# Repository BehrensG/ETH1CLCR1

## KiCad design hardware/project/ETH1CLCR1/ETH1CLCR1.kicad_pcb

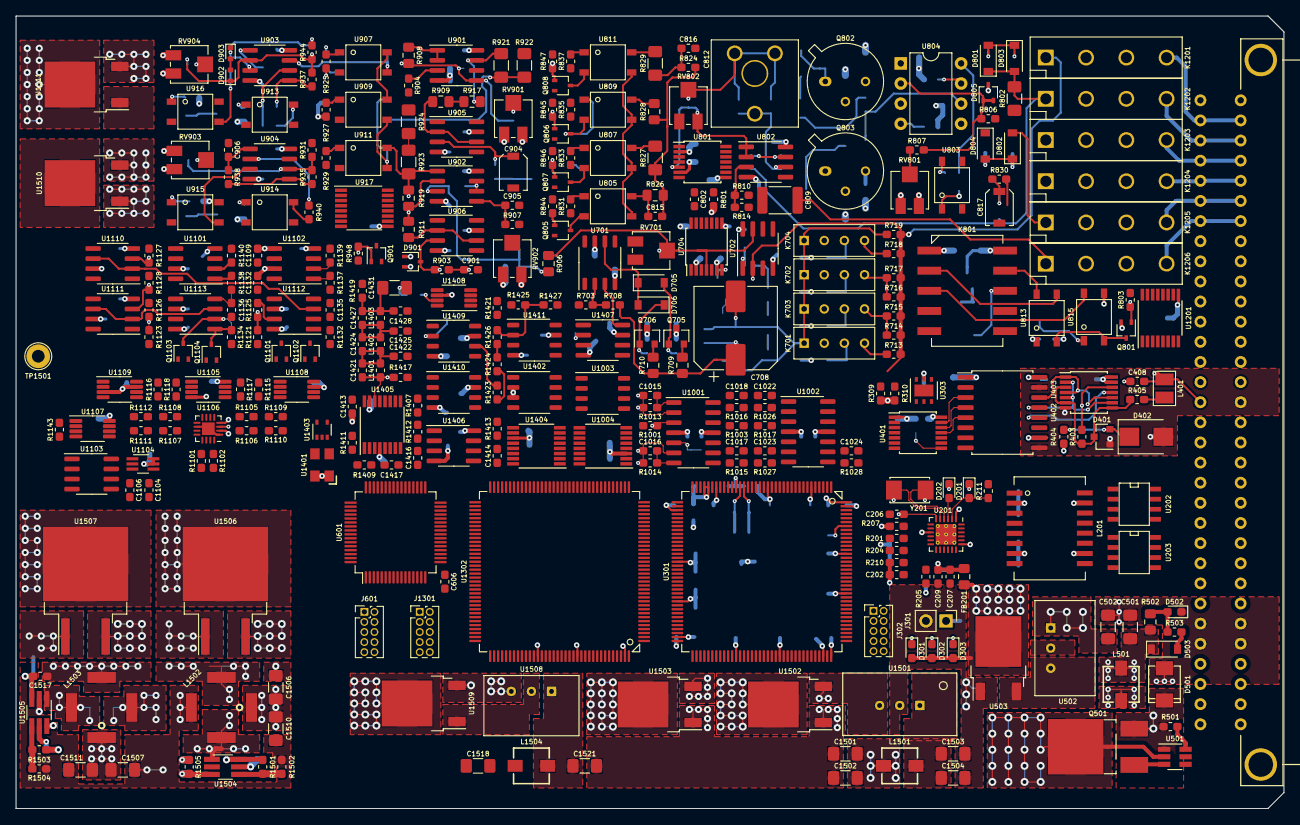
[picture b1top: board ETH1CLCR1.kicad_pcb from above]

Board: 8 copper layers, 160.0 x 100.0 mm, 744 parts (0 on the bottom side), 493 nets.

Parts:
C201, C204, C303, C305, C612, C613, C1302, C1304: 8p; C_0603_1608Metric_Pad1.05x0.95mm_HandSolder
C202, C205, C208, C209, C210, C211, C212, C301, C302, C304, C306, C308, C310, C312, C313, C314, C315, C316, C317, C318, C319, C321, C322, C401, C402, C403, C405, C407, C601, C602, C603, C604, C605, C606, C608, C611, C705, C706, C707, C709, C710, C711, C712, C803, C804, C805, C806, C807, C808, C810, C901, C902, C911, C912, C913, C914, C915, C916, C917, C918, C919, C920, C921, C922, C923, C1001, C1003, C1005, C1006, C1007, C1009, C1010, C1101, C1105, C1106, C1108, C1109, C1110, C1113, C1114, C1115, C1116, C1117, C1118, C1119, C1120, C1123, C1124, C1125, C1126, C1127, C1128, C1129, C1130, C1131, C1132, C1139, C1140, C1201, C1301, C1303, C1305, C1308, C1309, C1311, C1312, C1313, C1314, C1315, C1316, C1317, C1319, C1401, C1402, C1404, C1405, C1407, C1408, C1409, C1410, C1411, C1412, C1415, C1416, C1418, C1423, C1426, C1429, C1430, C1432, C1433, C1437, C1438: 100n; C_0603_1608Metric_Pad1.05x0.95mm_HandSolder
C203: 470p; C_0603_1608Metric_Pad1.05x0.95mm_HandSolder
C206, C207, C311, C320, C404, C406, C607, C609, C714, C802, C1004, C1008, C1103, C1104, C1107, C1310, C1318, C1406, C1512, C1513: 1u; C_0603_1608Metric_Pad1.05x0.95mm_HandSolder
C213, C214: 1n/1kV; C_1206_3216Metric_Pad1.42x1.75mm_HandSolder
C307, C309, C610, C1306, C1307: 2u2; C_0805_2012Metric_Pad1.15x1.40mm_HandSolder
C408, C813: 47p; C_0603_1608Metric_Pad1.05x0.95mm_HandSolder
C501, C502, C1501, C1502, C1503, C1504, C1506, C1507, C1518, C1521: 10u/50V; C_1206_3216Metric_Pad1.42x1.75mm_HandSolder
C503, C504, C1505, C1508, C1509, C1526, C1529: 10u/16V; C_1206_3216Metric_Pad1.42x1.75mm_HandSolder
C701, C702, C703, C704, C801, C818, C819, C820, C821, C822, C908, C909, C910, C1133, C1134, C1137, C1138: 10p; C_0603_1608Metric_Pad1.05x0.95mm_HandSolder
C708: 220u; CP_Elec_10x10
C713: 43p/200V; C_0603_1608Metric_Pad1.05x0.95mm_HandSolder
C715, C716, C823, C824: 10u/35V; C_1206_3216Metric_Pad1.42x1.75mm_HandSolder
C809: 1u/100V; C_1812_4532Metric_Pad1.30x3.40mm_HandSolder
C811: C; C_0603_1608Metric_Pad1.05x0.95mm_HandSolder
C812: BFC280908002; BFC2
C814: 33p/200V; C_0603_1608Metric_Pad1.05x0.95mm_HandSolder
C815: 6800p/200V; C_0603_1608Metric_Pad1.05x0.95mm_HandSolder
C816: 39p; C_0603_1608Metric_Pad1.05x0.95mm_HandSolder
C817, C904: JZ100; JZ
C903: 7p5; C_0603_1608Metric_Pad1.05x0.95mm_HandSolder
C905: 15p; C_0603_1608Metric_Pad1.05x0.95mm_HandSolder
C906: 390p; C_0603_1608Metric_Pad1.05x0.95mm_HandSolder
C907: 220p; C_0603_1608Metric_Pad1.05x0.95mm_HandSolder
C1002, C1102, C1403, C1435: 10u; C_0805_2012Metric_Pad1.15x1.40mm_HandSolder
C1011, C1012, C1013, C1014, C1019, C1020, C1021, C1414: 220n; C_0603_1608Metric_Pad1.05x0.95mm_HandSolder
C1015, C1016, C1017, C1018, C1022, C1023, C1024, C1121, C1122, C1135, C1136, C1419: 1n; C_0603_1608Metric_Pad1.05x0.95mm_HandSolder
C1111, C1112: 3300p; C_0603_1608Metric_Pad1.05x0.95mm_HandSolder
C1413, C1417: 10n; C_0603_1608Metric_Pad1.05x0.95mm_HandSolder
C1420, C1428: 22p; C_0603_1608Metric_Pad1.05x0.95mm_HandSolder
C1421, C1516, C1517: 4p7; C_0603_1608Metric_Pad1.05x0.95mm_HandSolder
C1422, C1425: 56p; C_0603_1608Metric_Pad1.05x0.95mm_HandSolder
C1424: 18p; C_0603_1608Metric_Pad1.05x0.95mm_HandSolder
C1427: 12p; C_0603_1608Metric_Pad1.05x0.95mm_HandSolder
C1431: 10u; C_1206_3216Metric_Pad1.42x1.75mm_HandSolder
C1434, C1436: 1p5; C_0603_1608Metric_Pad1.05x0.95mm_HandSolder
C1510, C1511, C1519, C1520, C1522, C1523, C1524, C1525, C1527, C1528: 4u7/50V; C_1206_3216Metric_Pad1.42x1.75mm_HandSolder
C1514, C1515: 1u/HC; C_1206_3216Metric_Pad1.42x1.75mm_HandSolder
D201: YELLOW; LED_0603_1608Metric_Pad1.05x0.95mm_HandSolder
D202, D302: GREEN; LED_0603_1608Metric_Pad1.05x0.95mm_HandSolder
D301, D502: RED; LED_0603_1608Metric_Pad1.05x0.95mm_HandSolder
D303: BLUE; LED_0603_1608Metric_Pad1.05x0.95mm_HandSolder
D401: BAV99; SOT-23
D402: SMBJ5.0A; D_SMB
D403: SD36C-01FTG; D_SOD-323_HandSoldering
D501: SM6T30AY; DO_214AA_REV
D503: MMSZ5249B; D_SOD-123
D701, D702, D703, D704, D705, D706, D801, D802, D803, D804, D806, D807, D808, D809, D810, D811, D812: 1N4148; D_SOD-123
D707, D708: CMDZ5256B TR; D_SOD-323_HandSoldering
D805, D901: BAT54SW; SOT-323_SC-70
D902, D903: MM5Z5V1T5G; D_SOD-523
D1401: SD103ATW; SOT-363_SC-70-6
D1501, D1502: PMEG6010EP,115; D_SOD-128
F501: MF-LSMF185/33X; Fuse_SMD2920
FB201, FB301, FB601, FB1301: 742792031; L_0805_2012Metric_Pad1.15x1.40mm_HandSolder
J301: Conn_02x01; PinHeader_1x02_P2.54mm_Vertical
J302, J601, J1301: 20021111-00010T4LF; PinHeader_2x05_P1.27mm_Vertical
J1201: C64AC; Socket_DIN41612-CaseC1-AC-Male-64Pin-2rows
K701, K702, K703, K704: 9012
K801: TQ2SA-5V; SA
K1201, K1202, K1203, K1204, K1205, K1206: HE3621A0510; HE360_x-5050462-8
L201: 749010012A
L401: CW252016-R33G; CW252016
L501, L1501, L1504: TCK-141
L1401, L1402, L1403: 4u7; L_0603_1608Metric_Pad1.05x0.95mm_HandSolder
L1502, L1503: 74489440068
Q501: IRFR5410; TO-252-2_Rectifier
Q701, Q702, Q703, Q704, Q801, Q804, Q805, Q806, Q807, Q808, Q901, Q902, Q903, Q1101, Q1102, Q1103, Q1104: BC847W; SOT-323_SC-70
Q705: MMBT4401L; SOT-23
Q706: MMBT4403L; SOT-23
Q802: 2N2218A; TO-39-3
Q803: 2N2904A; TO-39-3
R201, R202, R204, R205: 33; R_0603_1608Metric_Pad1.05x0.95mm_HandSolder
R203, R206, R207, R208, R209, R211, R304, R307, R308, R401, R603, R604, R701, R702, R704, R705, R718, R803, R810, R813, R815, R818, R824, R830, R841, R844, R845, R846, R847, R903, R904, R905, R907, R935, R938, R944, R948, R949, R950, R1122, R1124, R1135, R1136, R1139, R1141, R1142, R1303, R1304, R1401, R1405, R1407, R1424, R1428: 10k; R_0603_1608Metric_Pad1.05x0.95mm_HandSolder
R210: 1k5; R_0603_1608Metric_Pad1.05x0.95mm_HandSolder
R212: 12k1; R_0603_1608Metric_Pad1.05x0.95mm_HandSolder
R213, R214: 270; R_0603_1608Metric_Pad1.05x0.95mm_HandSolder
R215, R216, R217, R218: 49R9; R_0603_1608Metric_Pad1.05x0.95mm_HandSolder
R219: 1M/1kV; R_1206_3216Metric_Pad1.42x1.75mm_HandSolder
R220, R221: 75/1%; R_0603_1608Metric_Pad1.05x0.95mm_HandSolder
R301, R303, R831, R832, R833, R834, R835, R836, R837, R838, R925, R926, R927, R928, R929, R930, R936, R943, R945, R947: 680; R_0603_1608Metric_Pad1.05x0.95mm_HandSolder
R302: 560; R_0603_1608Metric_Pad1.05x0.95mm_HandSolder
R305, R306, R309, R310, R601, R602, R1301, R1302: 4k7; R_0603_1608Metric_Pad1.05x0.95mm_HandSolder
R402: 14k7; R_0603_1608Metric_Pad1.05x0.95mm_HandSolder
R403, R806, R1101, R1102, R1105, R1106, R1107, R1108, R1115, R1116, R1137, R1138: 100; R_0603_1608Metric_Pad1.05x0.95mm_HandSolder
R404, R931, R932, R937, R940, R942, R946, R1001, R1002, R1003, R1004, R1017, R1018, R1019, R1413, R1423, R1425, R1426, R1427: 1k; R_0603_1608Metric_Pad1.05x0.95mm_HandSolder
R405, R811, R812: 47; R_0603_1608Metric_Pad1.05x0.95mm_HandSolder
R406, R816, R817: 51R1; R_0603_1608Metric_Pad1.05x0.95mm_HandSolder
R501, R719, R939, R1013, R1014, R1015, R1016, R1026, R1027, R1028, R1127, R1128, R1131, R1132, R1133, R1134, R1416: 100k; R_0603_1608Metric_Pad1.05x0.95mm_HandSolder
R502: 6k8/0.5W; R_0805_2012Metric_Pad1.15x1.40mm_HandSolder
R503: 370; R_0603_1608Metric_Pad1.05x0.95mm_HandSolder
R703, R708, R716, R717: 2k; R_0603_1608Metric_Pad1.05x0.95mm_HandSolder
R706, R707: 15k; R_0603_1608Metric_Pad1.05x0.95mm_HandSolder
R709, R710: 27/.25W; R_0805_2012Metric_Pad1.15x1.40mm_HandSolder
R711: OPT; R_0603_1608Metric_Pad1.05x0.95mm_HandSolder
R712, R809, R840, R842, R843: 330; R_0603_1608Metric_Pad1.05x0.95mm_HandSolder
R713: 10; R_0603_1608Metric_Pad1.05x0.95mm_HandSolder
R714, R715: 200; R_0603_1608Metric_Pad1.05x0.95mm_HandSolder
R720: 56; R_0603_1608Metric_Pad1.05x0.95mm_HandSolder
R721: 205; R_0603_1608Metric_Pad1.05x0.95mm_HandSolder
R722, R801: 2k2; R_0603_1608Metric_Pad1.05x0.95mm_HandSolder
R723, R808: 550; R_0603_1608Metric_Pad1.05x0.95mm_HandSolder
R802: 1k/.25W; R_1206_3216Metric_Pad1.42x1.75mm_HandSolder
R804, R805: 21R5/.5W; R_0805_2012Metric_Pad1.15x1.40mm_HandSolder
R807: 10M; R_0603_1608Metric_Pad1.05x0.95mm_HandSolder
R814: 5M6; R_0603_1608Metric_Pad1.05x0.95mm_HandSolder
R819: 3k3; R_0603_1608Metric_Pad1.05x0.95mm_HandSolder
R820, R823: 261/.5W; R_0805_2012Metric_Pad1.15x1.40mm_HandSolder
R821, R822: 2R7/.5W; R_0805_2012Metric_Pad1.15x1.40mm_HandSolder
R825: 90k; R_1206_3216Metric_Pad1.42x1.75mm_HandSolder
R826: 10; R_0805_2012Metric_Pad1.15x1.40mm_HandSolder
R827, R922, R924: 100; R_1206_3216Metric_Pad1.42x1.75mm_HandSolder
R828: 1k01; R_0805_2012Metric_Pad1.15x1.40mm_HandSolder
R829: 1k; R_1206_3216Metric_Pad1.42x1.75mm_HandSolder
R839: 13R3; R_0603_1608Metric_Pad1.05x0.95mm_HandSolder
R901, R902, R914, R920, R933, R1143, R1501, R1503, R1505, R1507: 1M; R_0603_1608Metric_Pad1.05x0.95mm_HandSolder
R906, R908, R909, R910, R911, R913, R917, R919: 3k01; R_0805_2012Metric_Pad1.15x1.40mm_HandSolder
R912, R915, R918, R1403, R1404, R1422: DNP; R_0603_1608Metric_Pad1.05x0.95mm_HandSolder
R916: NC; R_0603_1608Metric_Pad1.05x0.95mm_HandSolder
R921, R923: 900; R_1206_3216Metric_Pad1.42x1.75mm_HandSolder
R934, R941: 22k; R_0603_1608Metric_Pad1.05x0.95mm_HandSolder
R1005, R1007, R1009, R1011, R1020, R1022, R1024, R1414: 24k9; R_0603_1608Metric_Pad1.05x0.95mm_HandSolder
R1006, R1008, R1010, R1012, R1021, R1023, R1025, R1415: 33k2; R_0603_1608Metric_Pad1.05x0.95mm_HandSolder
R1103, R1104: 590; R_0603_1608Metric_Pad1.05x0.95mm_HandSolder
R1109, R1110, R1111, R1112, R1129, R1130: 50; R_0603_1608Metric_Pad1.05x0.95mm_HandSolder
R1113, R1114: 499; R_0603_1608Metric_Pad1.05x0.95mm_HandSolder
R1117, R1118, R1121, R1123: 12k; R_0603_1608Metric_Pad1.05x0.95mm_HandSolder
R1119, R1120, R1125, R1126: 52k3; R_0603_1608Metric_Pad1.05x0.95mm_HandSolder
R1140: 10K; R_0603_1608Metric_Pad1.05x0.95mm_HandSolder
R1402, R1406, R1418, R1420, R1421: 0; R_0603_1608Metric_Pad1.05x0.95mm_HandSolder
R1408: 4k22; R_0603_1608Metric_Pad1.05x0.95mm_HandSolder
R1409, R1411: 3k9; R_0603_1608Metric_Pad1.05x0.95mm_HandSolder
R1410, R1412: 1k96; R_0603_1608Metric_Pad1.05x0.95mm_HandSolder
R1417, R1419: 300; R_0603_1608Metric_Pad1.05x0.95mm_HandSolder
R1502, R1504: 287k; R_0603_1608Metric_Pad1.05x0.95mm_HandSolder
R1506: 97k6; R_0603_1608Metric_Pad1.05x0.95mm_HandSolder
R1508: 46k4; R_0603_1608Metric_Pad1.05x0.95mm_HandSolder
RV701, RV802: 3314J-1-501E; Potentiometer_Bourns_3314J_Vertical
RV801: 3314J-1-203E; Potentiometer_Bourns_3314J_Vertical
RV901, RV902: 3314J-1-103E; Potentiometer_Bourns_3314J_Vertical
RV903, RV904: 3314J-2-104E; Potentiometer_Bourns_3314J_Vertical
TP1501: 5006; TestPoint_Loop_D2.60mm_Drill1.6mm_Beaded
U201: LAN8742A; QFN-24-1EP_4x4mm_P0.5mm_EP2.6x2.6mm_ThermalVias
U202, U203: LC03-3.3; SO8E
U301: STM32F765ZGT6; TQFP-144_20x20mm_P0.5mm
U302, U602, U1301: 24LC08B-E/MS; MSOP-8_3x3mm_P0.65mm
U303: HDC1080; Texas_PWSON-N6
U401: TXB0104PW; TSSOP-14_4.4x5mm_P0.65mm
U402: ADuM5402; SOIC-16W_7.5x10.3mm_P1.27mm
U403: 74AC125; TSSOP-14_4.4x5mm_P0.65mm
U501: MAX5902; SOT-23-6_Handsoldering
U502: TSR1-2450; TSR1
U503, U1502, U1503: LM1117DTX-3.3/NOPB; TO-252-2
U601: STM32F413RGT6Tx; LQFP-64_10x10mm_P0.5mm
U701, U1409, U1410, U1411: LT1468; SSOP-8_3.9x5.05mm_P1.27mm
U702, U802, U901, U902, U903, U904, U1406: TL072; SOIC-8_3.9x4.9mm_P1.27mm
U703, U803, U805, U806, U807, U808, U809, U810, U811, U812, U813, U814, U815, U907, U908, U909, U910, U911, U912, U913, U914, U915, U916: AQY212GS
U704, U801: AD5293BRUZ-20; TSSOP-14_4.4x5mm_P0.65mm
U804: HA3-2525-5Z; DIP-8_W7.62mm
U905, U906: TL071; SOIC-8_3.9x4.9mm_P1.27mm
U917, U1201: ULN2003A; TSSOP-16_4.4x5mm_P0.65mm
U1001, U1002: TL074; SOIC-14_3.9x8.7mm_P1.27mm
U1003, U1402: REF192; SSOP-8_3.9x5.05mm_P1.27mm
U1004: DAC8568IBPWR; TSSOP-16_4.4x5mm_P0.65mm
U1101, U1102: ADG419BR; SOIC-8_3.9x4.9mm_P1.27mm
U1103: ADR4525BRZ; SOIC-8_3.9x4.9mm_P1.27mm
U1104: ADA4807-1AKSZ-R2; SOT-363_SC-70-6_Handsoldering
U1105, U1107: ADA4807-2ARM; MSOP-8_3x3mm_P0.65mm
U1106: AD7380; LFCSP-16-1EP_3x3mm_P0.5mm_EP1.6x1.6mm
U1108, U1109: LT6350; MSOP-8_3x3mm_P0.65mm
U1110, U1111: OPA602; SOIC-8_3.9x4.9mm_P1.27mm
U1112, U1113: PGA103; SOIC-8_3.9x4.9mm_P1.27mm
U1302: STM32H743ZI; TQFP-144_20x20mm_P0.5mm
U1401: ECS-3225SMV-500-GP-TR; ECS
U1403: 74AHCT1G08; SOT-353_SC-70-5
U1404: AD5689BRUZ; TSSOP-16_4.4x5mm_P0.65mm
U1405: AD9835; TSSOP-16_4.4x5mm_P0.65mm
U1407: DG419LDY; SOIC-8_3.9x4.9mm_P1.27mm
U1408: AD5453YRMZ; MSOP-8_3x3mm_P0.65mm
U1501: TSR2-2450; TSR2
U1504, U1505: LT8330_S6; TSOT-23-6_HandSoldering
U1506: MC7815BD2TG; TO-263-2
U1507: MC7915BD2TG; TO-263-2
U1508: TSR1-2490; TSR1
U1509: LM1117DTX-5.0/NOPB; TO-252-2
U1510: MC78M12ABDTRKG; TO-252-2
U1511: MC79M12CDTG; TO-252-2
Y201: NX5032GA-25.000M-LN-CD-1; NX5032GA
Y301, Y601, Y1301: NX3225GD-8MHZ-STD-CRA-3; NX3225GD

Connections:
+3.3VF: C601.1, C602.1, C603.1, C604.1, C605.1, C606.1, C607.1, C608.1, C707.1, C810.1, C1007.1, C1008.1, C1108.1, C1109.1, C1110.1, C1113.1, C1401.1, C1402.1, C1404.1, C1435.1, C1437.1, C1509.1, FB601.2, J601.1, R601.1, R602.1, R604.2, R722.1, R801.1, R840.1, R842.1, R843.1, R1401.1, R1403.1, R1405.1, R1407.1, U601.1, U601.19, U601.32, U601.48, U601.64, U602.8, U704.8, U801.8, U1004.3, U1101.5, U1102.5, U1106.2, U1106.4, U1401.1, U1401.4, U1403.5, U1404.11, U1405.4, U1407.5, U1408.6, U1503.2
+3.3VP: C1301.1, C1303.1, C1305.1, C1308.1, C1309.1, C1310.1, C1311.1, C1312.1, C1313.1, C1314.1, C1315.1, C1316.1, C1317.1, C1508.1, FB1301.2, J1301.1, R1301.1, R1302.1, R1304.1, U1301.8, U1302.6, U1302.17, U1302.30, U1302.39, U1302.52, U1302.62, U1302.72, U1302.84, U1302.95, U1302.108, U1302.121, U1302.131, U1302.143, U1302.144, U1502.2
+3V3: C202.1, C205.1, C301.1, C302.1, C304.1, C306.1, C308.1, C310.1, C311.1, C312.1, C313.1, C314.1, C315.1, C316.1, C317.1, C318.1, C319.1, C322.1, C402.1, C504.1, D301.2, D302.2, D303.2, FB201.2, FB301.2, J302.1, R206.1, R207.1, R208.1, R209.1, R210.1, R304.2, R305.1, R306.1, R308.1, R309.1, R310.1, R401.1, U201.9, U301.6, U301.17, U301.30, U301.39, U301.52, U301.62, U301.72, U301.84, U301.95, U301.108, U301.121, U301.131, U301.143, U301.144, U302.8, U303.5, U401.1, U503.2
+5V: C401.1, C403.1, C404.1, C503.1, U401.14, U402.1, U502.3, U503.3
+5VF: C923.1, C1001.1, C1002.1, C1101.1, C1102.1, C1114.1, C1116.1, C1118.1, C1120.1, C1124.1, C1201.1, C1403.1, C1405.1, C1407.1, C1413.1, C1529.1, D701.1, D702.1, D703.1, D704.1, D812.1, K701.2, K702.2, K703.2, K704.2, K801.1, K1201.2, K1202.2, K1203.2, K1204.2, K1205.2, K1206.2, R831.2, R832.2, R833.2, R834.2, R835.2, R836.2, R837.2, R838.2, R925.2, R926.2, R927.2, R928.2, R929.2, R930.2, R936.1, R943.1, R945.1, R947.1, U917.9, U1003.2, U1003.3, U1103.2, U1104.5, U1104.6, U1105.8, U1107.8, U1108.3, U1108.7, U1109.3, U1109.7, U1201.9, U1402.2, U1402.3, U1404.5, U1405.15, U1509.2
+5V_TRIG: C405.1, C406.1, C407.1, R404.1, U402.10, U402.16, U403.13, U403.14
+12VF: C805.1, C823.1, C911.1, C912.1, C913.1, C914.1, C915.1, C916.1, C1527.1, D901.2, R811.2, R815.1, R820.1, RV801.1, RV901.3, RV902.3, RV903.1, RV904.1, U802.8, U901.8, U902.8, U903.8, U904.8, U905.7, U906.7, U1510.3
+15VF: C705.1, C709.1, C710.1, C715.1, C807.1, C1003.1, C1009.1, C1115.1, C1119.1, C1125.1, C1126.1, C1129.1, C1130.1, C1408.1, C1409.1, C1423.1, C1429.1, C1433.1, C1524.1, Q705.3, R706.1, R1131.2, R1132.2, R1133.2, R1134.2, U701.7, U702.8, U704.6, U801.6, U1001.4, U1002.4, U1101.4, U1102.4, U1110.7, U1111.7, U1112.8, U1113.8, U1406.8, U1407.4, U1409.7, U1410.7, U1411.7, U1506.3, U1510.1
+24V: F501.2, J1201.A31, J1201.A32, J1201.C31, J1201.C32
+24VDD: C501.1, C1501.1, C1502.1, C1506.1, C1507.1, C1510.1, C1511.1, C1518.1, D503.1, L501.1, L1501.1, L1502.1, L1503.1, L1504.1, Q501.2, R502.1, R1501.1, R1503.1, U501.2, U1504.6, U1505.6
-12VF: C806.1, C824.1, C917.1, C918.1, C919.1, C920.1, C921.1, C922.1, C1528.1, D901.1, R812.1, R818.2, R823.2, R912.1, R915.1, RV801.3, RV901.1, RV902.1, RV903.3, RV904.3, U802.4, U901.4, U902.4, U903.4, U904.4, U905.4, U906.4, U1511.3
-15VF: C706.1, C711.1, C712.1, C716.1, C808.1, C1005.1, C1010.1, C1117.1, C1123.1, C1127.1, C1128.1, C1131.1, C1132.1, C1411.1, C1415.1, C1426.1, C1430.1, C1432.1, C1525.1, Q706.3, R707.2, U701.4, U702.4, U704.2, U801.2, U1001.11, U1002.11, U1101.7, U1102.7, U1110.4, U1111.4, U1112.6, U1113.6, U1406.4, U1407.7, U1409.4, U1410.4, U1411.4, U1507.3, U1511.2
/ADC/ADC_NULL1: U1102.6, U1302.140
/ADC/ADC_NULL2: U1101.6, U1302.139
/ADC/ADC_OFFS1: C1022.1, R1026.1, R1127.1, U1002.1
/ADC/ADC_OFFS2: C1023.1, R1027.1, R1128.1, U1002.7
/ADC/ADC_REF: R1121.1, R1123.1, U1107.1, U1107.2
/ADC/ADC_SCLK: U1106.16, U1302.41
/ADC/ADC_SDI: U1106.15, U1302.43
/ADC/ADC_SDOA: R1101.2, U1302.42
/ADC/ADC_~ALARM: R1102.2, U1302.37
/ADC/ADC_~CS: U1106.12, U1302.40
/ADC/Em: U915.4, U1101.8
/ADC/Eref: U916.4, U1102.8
/ADC/G1A0_CTR: R1136.1, U1302.135
/ADC/G1A1_CTR: R1135.1, U1302.134
/ADC/G2A0_CTR: R1142.1, U1302.137
/ADC/G2A1_CTR: R1141.1, U1302.136
/ADC/GAIN1A0: Q1102.3, R1132.1, U1112.1
/ADC/GAIN1A1: Q1101.3, R1131.1, U1112.2
/ADC/GAIN2A0: Q1104.3, R1134.1, U1113.1
/ADC/GAIN2A1: Q1103.3, R1133.1, U1113.2
/ADC/REF2V5: C1104.1, C1106.1, R1103.2, R1143.1, U1103.6, U1104.3, U1107.3
/ADC/REFIO: C1107.1, U1104.1, U1104.4, U1106.11
/ADC/VCM: R1113.2, R1114.2, U1107.6, U1107.7
/Connector/A: J1201.A2, J1201.C2, K1201.4
/Connector/B: J1201.A3, J1201.C3, K1202.4
/Connector/C: J1201.A4, J1201.C4, K1203.4
/Connector/CXN_REL1: U1201.6, U1302.87
/Connector/CXN_REL2: U1201.5, U1302.88
/Connector/CXN_REL3: U1201.4, U1302.89
/Connector/CXN_REL4: U1201.3, U1302.90
/Connector/CXN_REL5: U1201.2, U1302.91
/Connector/CXN_REL6: U1201.1, U1302.92
/Connector/D: J1201.A5, J1201.C5, K1204.4
/Connector/E: J1201.A6, J1201.C6, K1205.4
/Connector/EXT_TRIG: C408.1, D403.1, J1201.A16, L401.1
/Connector/F: J1201.A7, J1201.C7, K1206.4
/Connector/HCUR: K1201.1, R713.1, R714.1, R715.1, R716.1, R717.1, R718.1, R719.1, R720.1, R721.2, U702.2
/Connector/HPOT: C809.2, C901.2, K1206.1
/Connector/LCUR: C814.1, C815.2, D801.1, D803.2, K1202.1, R802.1, R824.2, R825.2, R826.2, R827.2, R828.2, R904.2
/Connector/LPOT: D802.2, D804.1, K1205.1, R802.2, R806.2, R907.2
/Connector/RX+: J1201.A20, U203.8
/Connector/RX-: J1201.A21, U203.5
/Connector/TX+: J1201.C20, U202.8
/Connector/TX-: J1201.C21, U202.5
/DAC/+2V5REF: C1004.1, C1006.1, R1005.2, R1007.2, R1009.2, R1011.2, R1020.2, R1022.2, R1024.2, U1003.6, U1004.8
/DAC/DAC_ADC_OFFS1: R1017.2, U1004.6
/DAC/DAC_ADC_OFFS2: R1018.2, U1004.11
/DAC/DAC_DIN: U1004.15, U1302.21
/DAC/DAC_PA_OFFS1: R1001.2, U1004.4
/DAC/DAC_PA_OFFS2: R1002.2, U1004.13
/DAC/DAC_PA_OFFS3: R1003.2, U1004.5
/DAC/DAC_PA_OFFS4: R1004.2, U1004.12
/DAC/DAC_RR_OFFS1: R1019.2, U1004.7
/DAC/DAC_SCLK: U1004.16, U1302.19
/DAC/DAC_~CLR: U1004.9, U1302.14
/DAC/DAC_~LDAC: U1004.1, U1302.15
/DAC/DAC_~SYNC: U1004.2, U1302.18
/DAC/PA_OFFS1: C1015.1, R920.1, R1013.1, RV902.2, U1001.1
/DAC/PA_OFFS2: C1016.1, R914.1, R1014.1, RV901.2, U1001.7
/DAC/PA_OFFS3: C1017.1, R933.2, R1015.1, RV903.2, U1001.8
/DAC/PA_OFFS4: C1018.1, R939.2, R1016.1, RV904.2, U1001.14
/DAC/RR_OFFS1: C1024.1, R807.1, R1028.1, RV801.2, U1002.8
/Ethernet/ETH_RXN: L201.8, R218.2, U201.22
/Ethernet/ETH_RXP: L201.6, R217.2, U201.23
/Ethernet/ETH_TXN: L201.3, R216.2, U201.20
/Ethernet/ETH_TXP: L201.1, R215.2, U201.21
/Ethernet/MODE0: R201.1, R206.2, U201.8
/Ethernet/MODE1: R202.1, R207.2, U201.7
/Ethernet/MODE2: R204.1, R208.2, U201.11
/Ethernet/NRST: C321.1, J302.10, R308.2, U201.15, U301.25
/Ethernet/REFCLK0: R205.1, R209.2, U201.14
/Ethernet/REF_CLK: R205.2, U301.35
/Ethernet/RMII_CRS_DV: R204.2, U301.43
/Ethernet/RMII_MDC: U201.13, U301.27
/Ethernet/RMII_MDIO: R210.2, U201.12, U301.36
/Ethernet/RMII_RXD0: R201.2, U301.44
/Ethernet/RMII_RXD1: R202.2, U301.45
/Ethernet/RMII_TXD0: U201.17, U301.128
/Ethernet/RMII_TXD1: U201.18, U301.129
/Ethernet/RMII_TXEN: U201.16, U301.126
/FGEN Buffer + Source resistor/FB_CAP: R712.1, U1302.124
/FGEN Buffer + Source resistor/FB_CLK: U704.11, U1302.128
/FGEN Buffer + Source resistor/FB_RDY: R722.2, U704.14, U1302.125
/FGEN Buffer + Source resistor/FB_SDI: U704.10, U1302.129
/FGEN Buffer + Source resistor/FB_SDO: U704.13, U1302.127
/FGEN Buffer + Source resistor/FB_~CS: U704.12, U1302.93
/FGEN Buffer + Source resistor/FB_~RST: U704.1, U1302.126
/FGEN Buffer + Source resistor/FGEN: U701.3, U1407.8
/FGEN Buffer + Source resistor/SR_1KCTR: R702.1, U1302.119
/FGEN Buffer + Source resistor/SR_10CTR: R705.1, U1302.123
/FGEN Buffer + Source resistor/SR_10KCTR: R701.1, U1302.118
/FGEN Buffer + Source resistor/SR_100CTR: R704.1, U1302.122
/FGEN Buffer + Source resistor/TRIM_3: C713.1, R723.2, RV701.3, U702.6, U704.3
/FGEN Buffer + Source resistor/VLI: R723.1, R906.2, RV701.2, U702.7, U704.4
/FGEN/+2V5REF: C1406.1, C1438.1, R1408.2, R1414.2, U1402.6, U1404.1
/FGEN/ANALOG_SWITCH: U601.37, U1407.6
/FGEN/DDS_DAC_RSTSEL: R1402.2, U601.14
/FGEN/DDS_DAC_SCLK: U601.21, U1404.12
/FGEN/DDS_DAC_SDIN: U601.23, U1404.14
/FGEN/DDS_DAC_SDO: U601.22, U1404.8
/FGEN/DDS_DAC_~LDAC: U601.16, U1404.9
/FGEN/DDS_DAC_~RESET: R1405.2, U601.17, U1404.15
/FGEN/DDS_DAC_~SYNC: R1401.2, U601.50, U1404.13
/FGEN/DDS_FGEN_FSELECT: U601.28, U1405.10
/FGEN/DDS_FGEN_PSEL0: U601.41, U1405.12
/FGEN/DDS_FGEN_PSEL1: U601.42, U1405.11
/FGEN/DDS_FGEN_SCLK: U601.26, U1405.7
/FGEN/DDS_FGEN_SDATA: U601.43, U1405.8
/FGEN/DDS_FGEN_~FSYNC: R1407.2, U601.27, U1405.9
/FGEN/DDS_MDAC_DIN: U601.15, U1408.4
/FGEN/DDS_MDAC_SCLK: U601.34, U1408.3
/FGEN/DDS_MDAC_~SYNC: U601.33, U1408.5
/FGEN/V_AMPL: C1418.1, R1408.1, R1409.2, R1418.1, U1405.2
/FGEN/V_OFFSET: C1419.1, R1416.1, R1425.2, U1406.7
/MCU1/I2C_SCL: R306.2, U301.54, U302.6
/MCU1/I2C_SDA: R305.2, U301.55, U302.5
/MCU1/I2C_WP: U301.53, U302.7
/MCU1/MCU1_GPIO_OUT1: U301.22, U1302.7
/MCU1/MCU1_GPIO_OUT2: U301.26, U1302.8
/MCU1/MCU1_MCLK: U301.19, U1302.1
/MCU1/MCU1_MISO: U301.20, U1302.4
/MCU1/MCU1_MOSI: U301.21, U1302.5
/MCU1/MCU1_STATUS_IN: U301.28, U1302.9
/MCU1/MCU1_~SS: U301.18, U1302.3
/MCU1/MCU_DEFAULT: J301.1, R304.1, U301.104
/MCU1/MCU_VDDA: C320.1, FB301.1, U301.32, U301.33
/MCU1/SENS_SCL: R309.2, U301.11, U303.6
/MCU1/SENS_SDA: R310.2, U301.10, U303.1
/MCU1/TCK_SWCLK: J302.4, U301.109
/MCU1/TDI: J302.8, U301.110
/MCU1/TDO: J302.6, U301.133
/MCU1/TMS_SWDIO: J302.2, U301.105
/MCU1/TRIG_EN: U301.74, U401.2
/MCU1/TRIG_IN: U301.76, U401.4
/MCU1/TRIG_OUT: U301.75, U401.3
/MCU2/EEPROM_SCL: R1302.2, U1301.6, U1302.54
/MCU2/EEPROM_SDA: R1301.2, U1301.5, U1302.55
/MCU2/EEPROM_WP: U1301.7, U1302.53
/MCU2/MCU3_MISO: U601.52, U1302.112
/MCU2/MCU3_MOSI: U601.53, U1302.48
/MCU2/MCU3_NSS: U601.20, U1302.110
/MCU2/MCU3_SCLK: U601.51, U1302.111
/MCU2/MCU_NRST: C1319.1, J1301.10, R1304.2, U1302.25
/MCU2/MCU_VDDA: C1318.1, FB1301.1, U1302.32, U1302.33
/MCU2/PA_50MV: R948.1, U1302.60
/MCU2/PA_EM: R949.1, U1302.59
/MCU2/PA_ER: R950.1, U1302.58
/MCU2/PA_MOS1: U917.1, U1302.63
/MCU2/PA_MOS2: U917.2, U1302.64
/MCU2/PA_MOS3: U917.3, U1302.65
/MCU2/PA_MOS4: U917.4, U1302.66
/MCU2/PA_MOS5: U917.5, U1302.67
/MCU2/PA_MOS6: U917.6, U1302.68
/MCU2/RR_1KCRT: R845.1, U1302.80
/MCU2/RR_10CRT: R844.1, U1302.78
/MCU2/RR_10KCRT: R847.1, U1302.81
/MCU2/RR_100CRT: R846.1, U1302.79
/MCU2/RR_100KCRT: R803.1, U1302.82
/MCU2/RR_CLK: U801.11, U1302.69
/MCU2/RR_HA3-COMP: R809.1, U1302.86
/MCU2/RR_RDY: R801.2, U801.14, U1302.26
/MCU2/RR_RELAYCTR: R841.1, U1302.85
/MCU2/RR_SDI: U801.10, U1302.27
/MCU2/RR_SDO: U801.13, U1302.28
/MCU2/RR_~CS: U801.12, U1302.73
/MCU2/RR_~RST: U801.1, U1302.29
/MCU2/TCK_SWCLK: J1301.4, U1302.109
/MCU2/TMS_SWDIO: J1301.2, U1302.105
/MCU3/EEPROM_SCL: R602.2, U601.58, U602.6
/MCU3/EEPROM_SDA: R601.2, U601.59, U602.5
/MCU3/EEPROM_WP: U601.57, U602.7
/MCU3/MCU_NRST: C611.1, J601.10, R604.1, U601.7
/MCU3/TCK_SWCLK: J601.4, U601.49
/MCU3/TMS_SWDIO: J601.2, U601.46
/MCU3/VDDA: C609.1, FB601.1, U601.13
/Process Amplifier/50MV_NPN: Q901.3, U913.2, U914.2
/Process Amplifier/EM_NPN: Q902.3, U915.2
/Process Amplifier/ER_NPN: Q903.3, U916.2
/Process Amplifier/Err: C902.2, K801.2, U813.3
/Process Amplifier/MOS1: U907.2, U917.16
/Process Amplifier/MOS2: U908.2, U917.15
/Process Amplifier/MOS3: U909.2, U917.14
/Process Amplifier/MOS4: U910.2, U917.13
/Process Amplifier/MOS5: U911.2, U917.12
/Process Amplifier/MOS6: U912.2, U917.11
/Range Resistors/100KNPN: Q801.3, U813.2, U814.2, U815.2
/Range Resistors/R1KNPN: Q806.3, U809.2, U810.2
/Range Resistors/R10KNPN: Q808.3, U811.2, U812.2
/Range Resistors/R10NPN: Q805.3, U805.2, U806.2
/Range Resistors/R100NPN: Q807.3, U807.2, U808.2
/Trigger/EXT_TRIG_SIGN: R402.1, U402.12, U403.11
/Trigger/TRIG_OUT_EN: U402.14, U403.1, U403.4, U403.10
/Trigger/TRIG_OUT_SIGN: U402.13, U403.2, U403.5, U403.9
AGNDF: C201.2, C202.2, C203.2, C204.2, C205.2, C206.2, C207.2, C208.2, C209.2, C210.2, C211.2, C212.2, C213.2, C301.2, C302.2, C303.2, C304.2, C305.2, C306.2, C307.2, C308.2, C309.2, C310.2, C311.2, C312.2, C313.2, C314.2, C315.2, C316.2, C317.2, C318.2, C319.2, C320.2, C321.2, C322.2, C401.2, C402.2, C403.2, C404.2, C501.2, C502.2, C503.2, C504.2, C601.2, C602.2, C603.2, C604.2, C605.2, C606.2, C607.2, C608.2, C609.2, C610.1, C611.2, C612.2, C613.2, C701.2, C702.2, C703.2, C704.2, C705.2, C706.2, C707.2, C709.2, C710.2, C711.2, C712.2, C714.2, C715.2, C716.2, C801.2, C802.2, C803.2, C804.1, C805.2, C806.2, C807.2, C808.2, C810.2, C816.2, C817.2, C818.2, C819.2, C820.2, C821.2, C822.2, C823.2, C824.2, C903.2, C904.2, C905.2, C906.2, C908.2, C909.2, C910.2, C911.2, C912.2, C913.2, C914.2, C915.2, C916.2, C917.2, C918.2, C919.2, C920.2, C921.2, C922.2, C923.2, C1001.2, C1002.2, C1003.2, C1004.2, C1005.2, C1006.2, C1007.2, C1008.2, C1009.2, C1010.2, C1011.2, C1012.2, C1013.2, C1014.2, C1019.2, C1020.2, C1021.2, C1101.2, C1102.2, C1103.2, C1104.2, C1105.2, C1106.2, C1107.2, C1108.2, C1109.2, C1110.2, C1113.2, C1114.2, C1115.2, C1116.2, C1117.2, C1118.2, C1119.2, C1120.2, C1121.2, C1122.2, C1123.2, C1124.2, C1125.2, C1126.2, C1127.2, C1128.2, C1129.2, C1130.2, C1131.2, C1132.2, C1133.2, C1134.2, C1135.2, C1136.2, C1137.2, C1138.2, C1139.2, C1140.2, C1201.2, C1301.2, C1302.2, C1303.2, C1304.2, C1305.2, C1306.2, C1307.2, C1308.2, C1309.2, C1310.2, C1311.2, C1312.2, C1313.2, C1314.2, C1315.2, C1316.2, C1317.2, C1318.2, C1319.2, C1401.2, C1402.2, C1403.2, C1404.2, C1405.2, C1406.2, C1407.2, C1408.2, C1409.2, C1410.2, C1411.2, C1414.2, C1415.2, C1416.1, C1417.2, C1418.2, C1420.2, C1422.2, C1423.2, C1425.2, C1426.2, C1428.2, C1429.2, C1430.2, C1432.2, C1433.2, C1435.2, C1437.2, C1438.2, C1501.2, C1502.2, C1503.2, C1504.2, C1505.2, C1506.2, C1507.2, C1508.2, C1509.2, C1510.2, C1511.2, C1512.2, C1513.2, C1518.2, C1519.2, C1520.2, C1521.2, C1522.2, C1523.2, C1524.2, C1525.2, C1526.2, C1527.2, C1528.2, C1529.2, D501.2, D502.1, D708.1, D805.3, D1501.1, J301.2, J302.3, J302.5, J601.3, J601.5, J1201.A27, J1201.A28, J1201.C27, J1201.C28, J1301.3, J1301.5, K1203.1, K1204.1, L1502.3, Q701.2, Q702.2, Q703.2, Q704.2, Q801.2, Q804.2, Q805.2, Q806.2, Q807.2, Q808.2, Q901.2, Q902.2, Q903.2, Q1101.2, Q1102.2, Q1103.2, Q1104.2, R203.2, R211.2, R212.1, R213.2, R214.2, R219.2, R307.2, R603.2, R703.2, R804.2, R805.1, R814.2, R901.1, R902.2, R913.2, R922.2, R924.2, R931.2, R942.2, R1006.2, R1008.2, R1010.2, R1012.2, R1021.2, R1023.2, R1025.2, R1104.2, R1119.2, R1120.2, R1122.2, R1124.2, R1129.2, R1130.2, R1139.1, R1140.1, R1143.2, R1303.2, R1404.2, R1409.1, R1411.2, R1415.2, R1417.2, R1419.2, R1428.1, R1502.2, R1504.2, R1506.2, R1508.2, RV802.1, TP1501.1, U201.25, U301.16, U301.31, U301.38, U301.51, U301.61, U301.83, U301.94, U301.107, U301.120, U301.130, U302.1, U302.2, U302.3, U302.4, U303.2, U401.7, U402.2, U402.8, U501.4, U502.2, U503.1, U601.12, U601.18, U601.31, U601.47, U601.63, U602.1, U602.2, U602.3, U602.4, U702.3, U702.5, U703.2, U704.9, U801.3, U801.9, U802.5, U803.2, U803.3, U804.3, U814.3, U815.3, U913.3, U914.3, U917.8, U1002.12, U1003.4, U1004.14, U1101.3, U1102.3, U1103.4, U1104.2, U1105.4, U1106.1, U1106.10, U1106.17, U1107.4, U1108.6, U1109.6, U1201.8, U1301.1, U1301.2, U1301.3, U1301.4, U1302.16, U1302.31, U1302.38, U1302.51, U1302.61, U1302.83, U1302.94, U1302.107, U1302.120, U1302.130, U1401.2, U1402.4, U1403.3, U1404.4, U1404.10, U1405.5, U1405.13, U1407.3, U1408.2, U1409.3, U1410.3, U1411.3, U1501.2, U1502.1, U1503.1, U1504.2, U1505.2, U1506.2, U1507.1, U1508.2, U1509.1, U1510.2, U1511.1
Earth: C213.1, C214.2, J1201.A18, J1201.A22, J1201.C18, J1201.C22, R219.1
GND_TRIG: C405.2, C406.2, C407.2, D401.1, D402.2, D403.2, J1201.C16, R406.2, U402.9, U402.15, U403.7
unnamed: C201.1, U201.5, Y201.2
unnamed: C203.1, C206.1, U201.6
unnamed: C204.1, U201.4, Y201.1
unnamed: C214.1, R220.2, R221.2
unnamed: C303.1, U301.23, Y301.1
unnamed: C305.1, U301.24, Y301.2
unnamed: C307.1, U301.71
unnamed: C309.1, U301.106
unnamed: C408.2, R406.1
unnamed: C502.1, L501.2, U502.1
unnamed: C610.2, U601.30
unnamed: C612.1, U601.6, Y601.2
unnamed: C613.1, U601.5, Y601.1
unnamed: C701.1, Q701.1, R701.2
unnamed: C702.1, Q702.1, R702.2
unnamed: C703.1, Q703.1, R704.2
unnamed: C704.1, Q704.1, R705.2
unnamed: C708.1, R708.1, R709.2, R710.1, R711.2, U703.3
unnamed: C708.2, K701.1, K702.1, K703.1, K704.1, R711.1, R719.2, U703.4
unnamed: C713.2, R721.1, U702.1
unnamed: C714.1, U704.7
unnamed: C801.1, Q801.1, R803.2
unnamed: C802.1, U801.7
unnamed: C803.1, D801.2, D803.1, R804.1
unnamed: C804.2, D802.1, D804.2, R805.2
unnamed: C809.1, R810.2
unnamed: C811.1, C812.1, R813.1, R819.2, U802.6
unnamed: C811.2, C812.2, R808.1, R813.2, RV802.2, U801.4
unnamed: C813.1, U803.4
unnamed: C813.2, U804.8
unnamed: C814.2, R819.1, U802.7
unnamed: C815.1, R826.1, U805.4, U806.4
unnamed: C816.1, R824.1, R829.2
unnamed: C817.1, R825.1, R830.2
unnamed: C818.1, Q804.1, R841.2
unnamed: C819.1, Q805.1, R844.2
unnamed: C820.1, Q806.1, R845.2
unnamed: C821.1, Q807.1, R846.2
unnamed: C822.1, Q808.1, R847.2
unnamed: C901.1, R901.2, R903.2
unnamed: C902.1, R902.1, R905.2
unnamed: C903.1, D901.3, R903.1, U906.3
unnamed: C904.1, R905.1, U905.3
unnamed: C905.1, R907.1, U902.5
unnamed: C906.1, R938.1, U904.5
unnamed: C907.1, D903.1, R944.1, R946.2, U903.7
unnamed: C907.2, D902.1, R937.1, R939.1, R944.2, U903.6
unnamed: C908.1, Q901.1, R948.2
unnamed: C909.1, Q902.1, R949.2
unnamed: C910.1, Q903.1, R950.2
unnamed: C1011.1, R1001.1, U1001.3
unnamed: C1012.1, R1002.1, U1001.5
unnamed: C1013.1, R1003.1, U1001.10
unnamed: C1014.1, R1004.1, U1001.12
unnamed: C1015.2, R1005.1, R1006.1, R1013.2, U1001.2
unnamed: C1016.2, R1007.1, R1008.1, R1014.2, U1001.6
unnamed: C1017.2, R1009.1, R1010.1, R1015.2, U1001.9
unnamed: C1018.2, R1011.1, R1012.1, R1016.2, U1001.13
unnamed: C1019.1, R1017.1, U1002.3
unnamed: C1020.1, R1018.1, U1002.5
unnamed: C1021.1, R1019.1, U1002.10
unnamed: C1022.2, R1020.1, R1021.1, R1026.2, U1002.2
unnamed: C1023.2, R1022.1, R1023.1, R1027.2, U1002.6
unnamed: C1024.2, R1024.1, R1025.1, R1028.2, U1002.9
unnamed: C1103.1, U1106.3
unnamed: C1105.1, U1106.9
unnamed: C1111.1, R1105.1, R1109.2
unnamed: C1111.2, R1106.1, R1110.2
unnamed: C1112.1, R1107.1, R1111.2
unnamed: C1112.2, R1108.1, R1112.2
unnamed: C1121.1, R1115.2, U1108.8
unnamed: C1122.1, R1116.2, U1109.8
unnamed: C1133.1, Q1101.1, R1135.2
unnamed: C1134.1, Q1102.1, R1136.2
unnamed: C1135.1, R1137.1, U1112.4
unnamed: C1136.1, R1138.1, U1113.4
unnamed: C1137.1, Q1103.1, R1141.2
unnamed: C1138.1, Q1104.1, R1142.2
unnamed: C1139.1, R1113.1, U1108.2
unnamed: C1140.1, R1114.1, U1109.2
unnamed: C1302.1, U1302.23, Y1301.1
unnamed: C1304.1, U1302.24, Y1301.2
unnamed: C1306.1, U1302.71
unnamed: C1307.1, U1302.106
unnamed: C1410.1, R1411.1, U1405.1
unnamed: C1412.1, R1418.2, U1406.1, U1406.2
unnamed: C1412.2, R1410.1, R1412.2
unnamed: C1413.2, U1405.16
unnamed: C1414.1, R1413.1, U1406.5
unnamed: C1416.2, D1401.1, D1401.5, R1412.1, U1406.3
unnamed: C1417.1, U1405.3
unnamed: C1419.2, R1414.1, R1415.1, R1416.2, U1406.6
unnamed: C1420.1, C1421.2, L1401.1, R1417.1, U1405.14
unnamed: C1421.1, C1422.1, C1424.2, L1401.2, L1402.1
unnamed: C1424.1, C1425.1, C1427.2, L1402.2, L1403.1
unnamed: C1427.1, C1428.1, C1431.2, L1403.2, R1419.1
unnamed: C1431.1, R1420.2
unnamed: C1434.1, R1421.1, R1423.2, U1409.6
unnamed: C1434.2, U1408.1, U1409.2
unnamed: C1436.1, R1424.1, R1426.2, U1410.6
unnamed: C1436.2, R1422.1, R1423.1, R1424.2, U1410.2
unnamed: C1503.1, C1504.1, L1501.2, U1501.1
unnamed: C1505.1, U1501.3, U1502.3, U1503.3
unnamed: C1512.1, U1504.5
unnamed: C1513.1, U1505.5
unnamed: C1514.1, D1502.2, L1502.2
unnamed: C1514.2, L1502.4, U1504.1
unnamed: C1515.1, D1501.2, L1503.2
unnamed: C1515.2, L1503.4, U1505.1
unnamed: C1516.1, C1519.1, C1522.1, D1502.1, R1505.1, U1506.1
unnamed: C1516.2, R1505.2, R1506.1, U1504.3
unnamed: C1517.1, C1520.1, C1523.1, L1503.3, R1507.1, U1507.2
unnamed: C1517.2, R1507.2, R1508.1, U1505.3
unnamed: C1521.1, L1504.2, U1508.1
unnamed: C1526.1, U1508.3, U1509.3
unnamed: D201.1, R213.1
unnamed: D201.2, R211.1, U201.2
unnamed: D202.1, R214.1
unnamed: D202.2, U201.3
unnamed: D301.1, R301.2
unnamed: D302.1, R302.2
unnamed: D303.1, R303.2
unnamed: D401.2, D402.1, R404.2
unnamed: D401.3, R403.2, R405.1, U403.3, U403.6, U403.8
unnamed: D501.1, F501.1, Q501.3, R501.1, U501.1
unnamed: D502.2, R502.2, R503.2
unnamed: D503.2, R503.1
unnamed: D701.2, K701.3, Q701.3
unnamed: D702.2, K702.3, Q702.3
unnamed: D703.2, K703.3, Q703.3
unnamed: D704.2, K704.3, Q704.3
unnamed: D705.1, D706.2, U701.6
unnamed: D705.2, Q705.1, R706.2
unnamed: D706.1, Q706.1, R707.1
unnamed: D707.1, R720.2
unnamed: D707.2, D708.2
unnamed: D805.1, D805.2, R806.1, R807.2, U804.2
unnamed: D806.1, R816.1
unnamed: D806.2, D808.1, Q802.2, R815.2
unnamed: D807.1, D809.2, Q803.2, R818.1
unnamed: D807.2, R817.2
unnamed: D808.2, D810.1
unnamed: D809.1, D811.2
unnamed: D810.2, Q802.1, R821.1
unnamed: D811.1, Q803.1, R822.2
unnamed: D812.2, K801.10, Q804.3
unnamed: D902.2, D903.2
unnamed: D1401.2, D1401.6, R1410.2, U1404.3
unnamed: K701.4, R713.2
unnamed: K702.4, R716.2, R717.2
unnamed: K703.4, R714.2, R715.2
unnamed: K704.4, R718.2
unnamed: K801.3, U805.3, U807.3, U809.3, U811.3, U815.4
unnamed: K801.8, R839.2, U808.3, U810.3, U812.3, U814.4
unnamed: K801.9, R821.2, R822.1, R830.1, U813.4
unnamed: K1201.3, U1201.11
unnamed: K1202.3, U1201.12
unnamed: K1203.3, U1201.13
unnamed: K1204.3, U1201.14
unnamed: K1205.3, U1201.15
unnamed: K1206.3, U1201.16
unnamed: L201.9, U203.4
unnamed: L201.10, R220.1
unnamed: L201.11, U203.1
unnamed: L201.14, U202.4
unnamed: L201.15, R221.1
unnamed: L201.16, U202.1
unnamed: L401.2, R405.2
unnamed: Q501.1, U501.3
unnamed: Q705.2, R709.1
unnamed: Q706.2, R710.2
unnamed: Q802.3, R820.2
unnamed: Q803.3, R823.1
unnamed: R203.1, U201.10
unnamed: R212.2, U201.24
unnamed: R301.1, U301.111
unnamed: R302.1, U301.112
unnamed: R303.1, U301.113
unnamed: R307.1, U301.138
unnamed: R401.2, U401.8
unnamed: R402.2, R403.1, U403.12
unnamed: R501.2, U501.6
unnamed: R603.1, U601.60
unnamed: R703.1, R708.2, U701.2
unnamed: R712.2, U703.1
unnamed: R808.2, RV802.3, U801.5, U802.1, U802.2
unnamed: R809.2, U803.1
unnamed: R810.1, R814.1, U802.3
unnamed: R811.1, U804.7
unnamed: R812.2, U804.4
unnamed: R816.2, R817.1, U804.6
unnamed: R827.1, U807.4, U808.4
unnamed: R828.1, U809.4, U810.4
unnamed: R829.1, U811.4, U812.4
unnamed: R831.1, U805.1
unnamed: R832.1, U806.1
unnamed: R833.1, U807.1
unnamed: R834.1, U808.1
unnamed: R835.1, U809.1
unnamed: R836.1, U810.1
unnamed: R837.1, U811.1
unnamed: R838.1, U812.1
unnamed: R839.1, U806.3
unnamed: R840.2, U813.1
unnamed: R842.2, U814.1
unnamed: R843.2, U815.1
unnamed: R904.1, U901.3
unnamed: R906.1, R910.1, R915.2, R920.2, U902.3
unnamed: R908.1, R912.2, R913.1, R914.2, U901.5
unnamed: R908.2, U901.1, U901.2
unnamed: R909.1, R916.2, R917.2, U901.6
unnamed: R909.2, U905.2, U905.6
unnamed: R910.2, U902.6, U902.7
unnamed: R911.1, R918.2, R919.2, U902.2
unnamed: R911.2, U906.2, U906.6
unnamed: R916.1, R917.1, R921.1, U901.7, U907.4, U909.4
unnamed: R918.1, R919.1, R923.1, U902.1, U908.4, U911.4
unnamed: R921.2, R922.1, U910.4
unnamed: R923.2, R924.1, U912.4
unnamed: R925.1, U907.1
unnamed: R926.1, U908.1
unnamed: R927.1, U909.1
unnamed: R928.1, U910.1
unnamed: R929.1, U911.1
unnamed: R930.1, U912.1
unnamed: R931.1, R933.1, R935.2, U904.2
unnamed: R932.1, R934.2, U903.2
unnamed: R932.2, U913.4
unnamed: R934.1, R937.2, U903.1
unnamed: R935.1, R938.2, U904.1
unnamed: R936.2, U913.1
unnamed: R940.1, R941.2, U904.6
unnamed: R940.2, U914.4
unnamed: R941.1, U904.7, U915.3
unnamed: R942.1, U903.5
unnamed: R943.2, U914.1
unnamed: R945.2, U915.1
unnamed: R946.1, U916.3
unnamed: R947.2, U916.1
unnamed: R1101.1, U1106.13
unnamed: R1102.1, U1106.14
unnamed: R1103.1, R1104.1, U1107.5
unnamed: R1105.2, U1106.6
unnamed: R1106.2, U1106.5
unnamed: R1107.2, U1106.8
unnamed: R1108.2, U1106.7
unnamed: R1109.1, U1108.1, U1108.4
unnamed: R1110.1, U1108.5
unnamed: R1111.1, U1109.1, U1109.4
unnamed: R1112.1, U1109.5
unnamed: R1115.1, R1117.2, U1105.7
unnamed: R1116.1, R1118.2, U1105.1
unnamed: R1117.1, R1119.1, U1105.6
unnamed: R1118.1, R1120.1, U1105.2
unnamed: R1121.2, R1122.1, R1125.2, U1105.5
unnamed: R1123.2, R1124.1, R1126.2, U1105.3
unnamed: R1125.1, U1112.7
unnamed: R1126.1, U1113.7
unnamed: R1127.2, R1129.1, U1110.3
unnamed: R1128.2, R1130.1, U1111.3
unnamed: R1137.2, U1102.1
unnamed: R1138.2, U1101.1
unnamed: R1139.2, U1102.2
unnamed: R1140.2, U1101.2
unnamed: R1303.1, U1302.138
unnamed: R1402.1, R1403.2, R1404.1, U1404.16
unnamed: R1406.1, U1403.4, U1405.6
unnamed: R1406.2, U1401.3, U1403.1, U1403.2
unnamed: R1413.2, U1404.7
unnamed: R1420.1, R1422.2, U1408.7
unnamed: R1421.2, U1408.8
unnamed: R1425.1, R1426.1, R1427.2, U1411.2
unnamed: R1427.1, U1407.1, U1411.6
unnamed: R1428.2, U1407.2
unnamed: R1501.2, R1502.1, U1504.4
unnamed: R1503.2, R1504.1, U1505.4
unnamed: U401.11, U402.5
unnamed: U401.12, U402.4
unnamed: U401.13, U402.3
unnamed: U903.3, U907.3, U908.3
unnamed: U904.3, U909.3, U910.3, U911.3, U912.3
unnamed: U1002.13, U1002.14
unnamed: U1110.2, U1110.6, U1112.3
unnamed: U1111.2, U1111.6, U1113.3
VCCQ: C207.1, C208.1, C209.1, C210.1, C211.1, C212.1, FB201.1, L201.2, L201.7, R215.1, R216.1, R217.1, R218.1, U201.1, U201.19

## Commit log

2019-12-05 Schematic design
2020-01-06 Need to redesign the AC source, the LT1468 is too slow.
2020-01-07 Footprint asigment (not finished).
2020-01-11 Modification in schematic and PCB layout.
2020-01-12 PCB layout
2020-01-15 Redesinged ADC schematic.
2020-01-16 Redesigned the power supply, added humidy+temp. sensor.
2020-01-18 Fixed mistake in ADC schematic.
2020-01-19 Changes in schematics.
2020-01-19 Checked the schematics. Created BOM.
2020-01-21 Fixed some mistakes in the foorpeints. BOM list ready.
2020-01-28 Changed op-amps in ADC schematic.
2020-01-30 PCB layout.
2020-02-02 PCB done.
2020-02-03 Small modification to silk screen
2020-02-05 Range BC847 base serial resistors value from 10k to 1k.
2020-02-06 Small modifications
2020-02-08 Fixed bug in STM32 symbols
2020-02-09 BOM list update
2020-02-17 Changed BC847W base resistor from 1k to 10k.
2020-02-28 Small changes in schematics and PCB
2020-02-28 Deleted software compilation objet files
2020-03-04 First software test on MCU1 (FreeRTOS, LwIP and SCPI parser).
2020-03-06 `vallen` is verified to be less than `len`, therefore, it can never be the case that `vallen >= len + sizeof(rhostname)`.
    This PR fixes the check so the `rhostname` array does not overflow.
    Reported-by: Github Security Lab <securitylab@github.com>
2020-03-15 Software development
2020-03-21 Software development of MCU1. Fixed problem with snprintf in FreeRTOS using solution from http://www.nadler.com/embedded/newlibAndFreeRTOS.html
2020-03-29 Softare development
2020-04-11 MCU3 software development
2020-04-13 Bug fixes in FGEN schematic. Software for AD9835 and AD5689 works.
2020-04-13 Fixed problem with LT1468 stablity (changed 1p5 to 27p C). AD5453 software works. Changed U1410 gain from 10 to 5.
2020-04-16 Software development.
2020-04-26 Was able to set the SPI3 (MCU2) to run with 80 MHZ clock speed with AD7380. Using HAL lib for SPI and GPIO, too slow switching. Need to change to LL with DMA.
2020-04-27 Low level GPIO and SPI. ADC register readout works.
2020-05-05 First test with SPI communication MCU1(Master) <-> MCU2(Slave) successful.
2020-05-11 Fixed problems with MCU1 and MCU2 IRQ communication (buffer problems and IRQ handler).
2020-05-17 SCPI function development.
2020-05-19 MCU1 software development.
2020-05-20 Added documentation to MCU1 SCPI functions.
2020-05-22 MCU1 SCPI functions development.
2020-05-28 Software development for MCU2 and MCU3
2020-06-13 Fixed Ethernet connection stability problems. Problem was the too small stack size for Ethernet thread in FreeRTOS.
2020-06-14 Fixed problem with the SPI communication between MCU1 and MCU2. Fixed the data format output in MCU1.
2020-06-14 Problem with MCU1 only write commands to MCU2.
2020-06-14 Fixed the MCU1 only TX commands to MCU2 (not the best solution). Changed the MCU2 output string.
2020-06-15 MCU3 and MCU2 SPI communication works.
2020-06-28 Fixed communication stability between MCU1 and MCU2. Fixed communication to ADC. DAC communication doesn't works. Voltages on LT6350 and PGA103 are not what expected (according to LTSpice).
